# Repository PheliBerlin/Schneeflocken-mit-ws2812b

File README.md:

# Schneeflocken-mit-ws2812b
Deko 2020 mit ws2812b und dem Attiny84

Die Platinen<br>

Nach dem Zusammenbau<br>

Zum Schluß mit Deko<br>

Das ganze ist skalierbar. Vier Sterne mit Deko, schon am Fenster aufgestellt.<br>

Programmiert habe ich das mit der Arduinoumgebung mit der FastLED Bibliothek, da gibt es Anleitungen massenhaft im Netz.

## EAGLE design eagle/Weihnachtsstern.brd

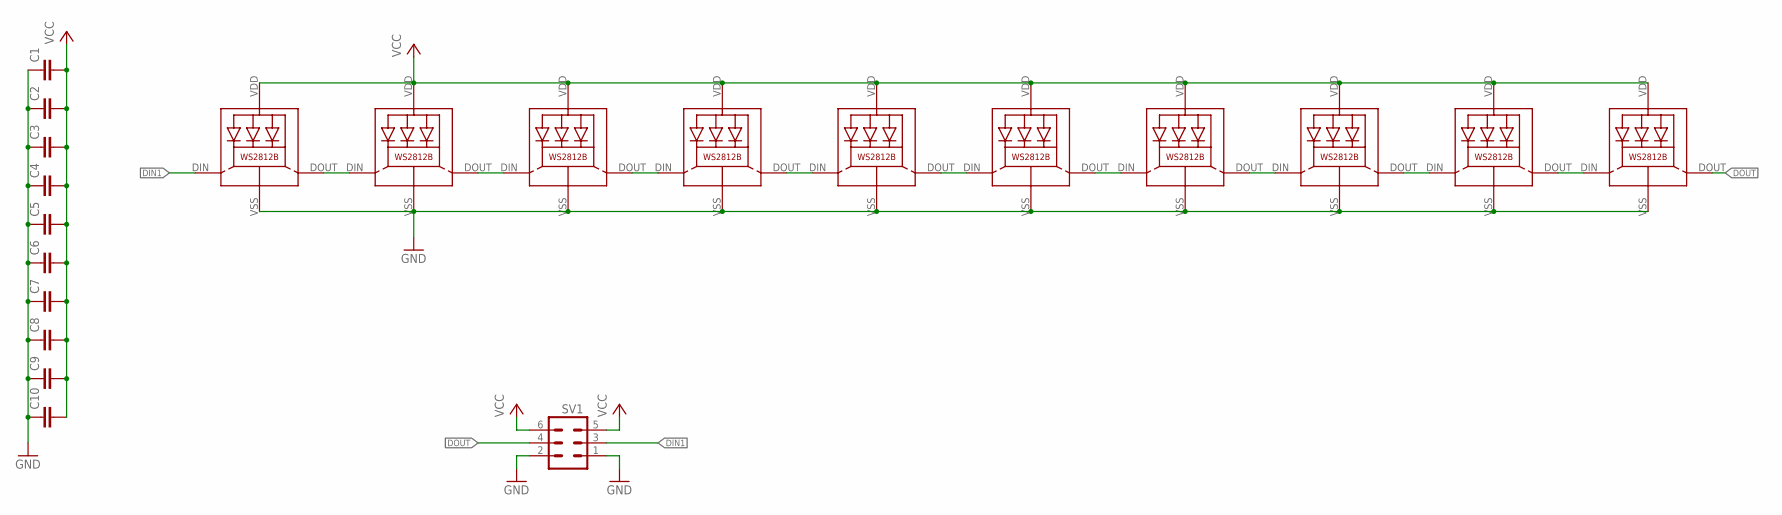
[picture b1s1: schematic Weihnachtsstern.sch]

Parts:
C1, C2, C3, C4, C5, C6, C7, C8, C9, C10: C-EUC0805; C0805
LED1, LED2, LED3, LED4, LED5, LED6, LED7, LED8, LED9, LED10: WS2812B
SV1: MA03-2

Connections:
DIN1: LED1.DIN (DI), SV1.3
DOUT: LED10.DOUT (DO), SV1.4
GND: C1.1, C2.1, C3.1, C4.1, C5.1, C6.1, C7.1, C8.1, C9.1, C10.1, LED1.VSS (GND), LED2.VSS (GND), LED3.VSS (GND), LED4.VSS (GND), LED5.VSS (GND), LED6.VSS (GND), LED7.VSS (GND), LED8.VSS (GND), LED9.VSS (GND), LED10.VSS (GND), SV1.1, SV1.2
unnamed: LED1.DOUT (DO), LED2.DIN (DI)
unnamed: LED2.DOUT (DO), LED3.DIN (DI)
unnamed: LED3.DOUT (DO), LED4.DIN (DI)
unnamed: LED4.DOUT (DO), LED5.DIN (DI)
unnamed: LED5.DOUT (DO), LED6.DIN (DI)
unnamed: LED6.DOUT (DO), LED7.DIN (DI)
unnamed: LED7.DOUT (DO), LED8.DIN (DI)
unnamed: LED8.DOUT (DO), LED9.DIN (DI)
unnamed: LED9.DOUT (DO), LED10.DIN (DI)
VCC: C1.2, C2.2, C3.2, C4.2, C5.2, C6.2, C7.2, C8.2, C9.2, C10.2, LED1.VDD, LED2.VDD, LED3.VDD, LED4.VDD, LED5.VDD, LED6.VDD, LED7.VDD, LED8.VDD, LED9.VDD, LED10.VDD, SV1.5, SV1.6

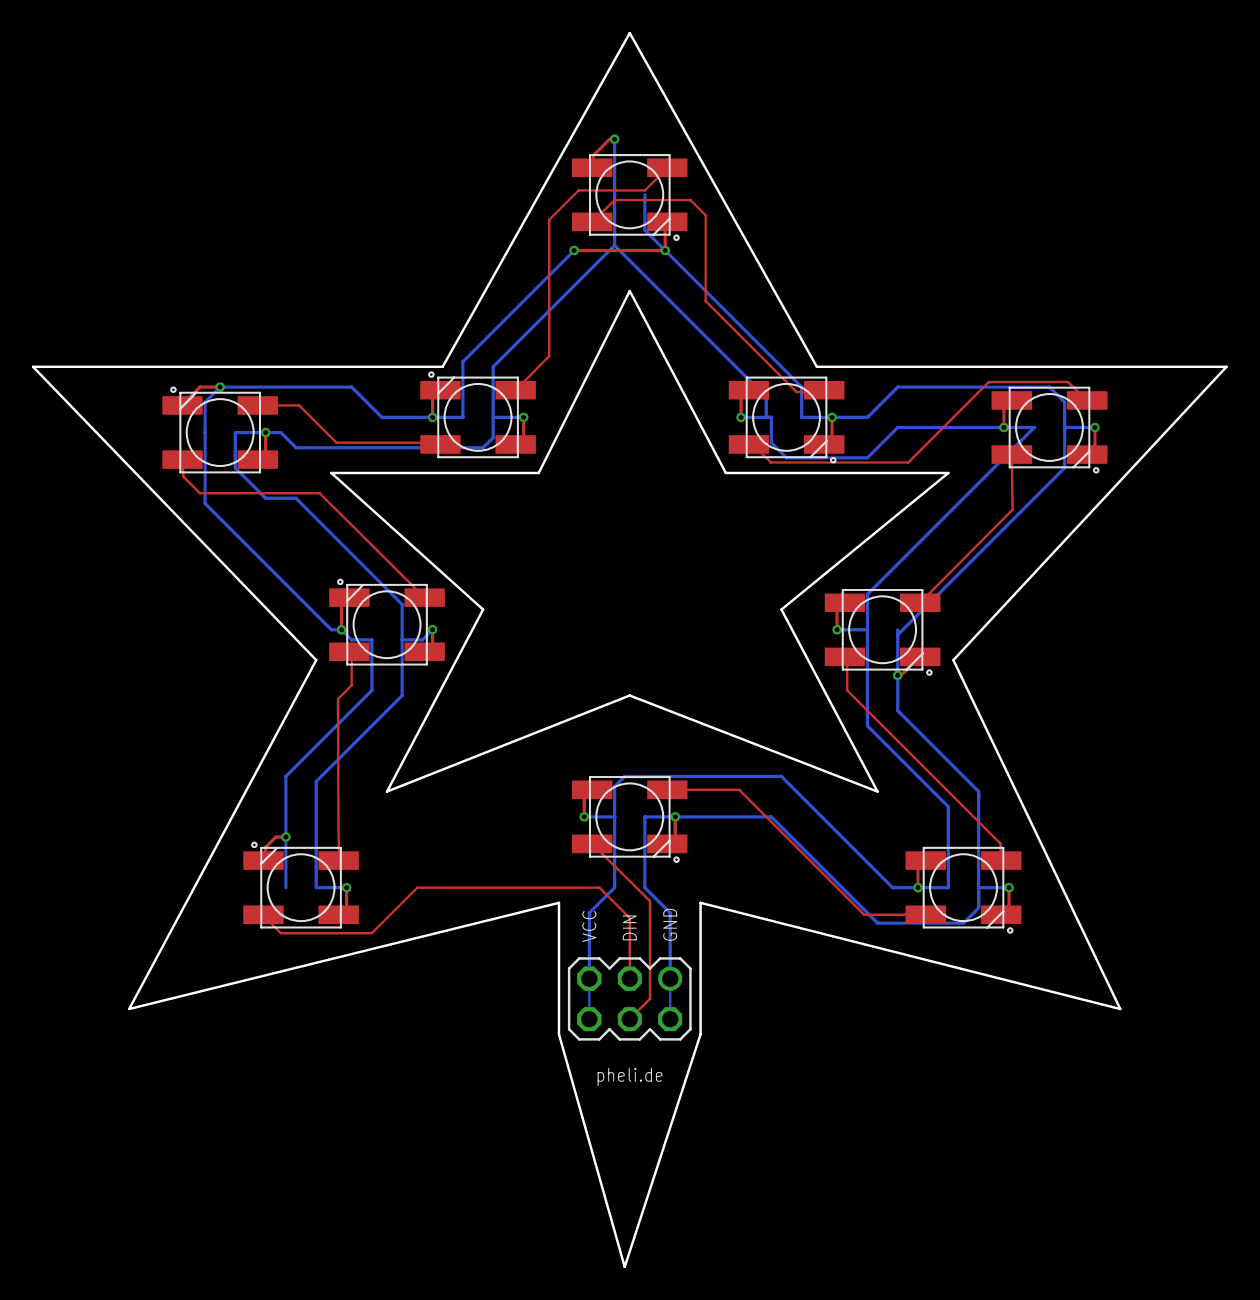
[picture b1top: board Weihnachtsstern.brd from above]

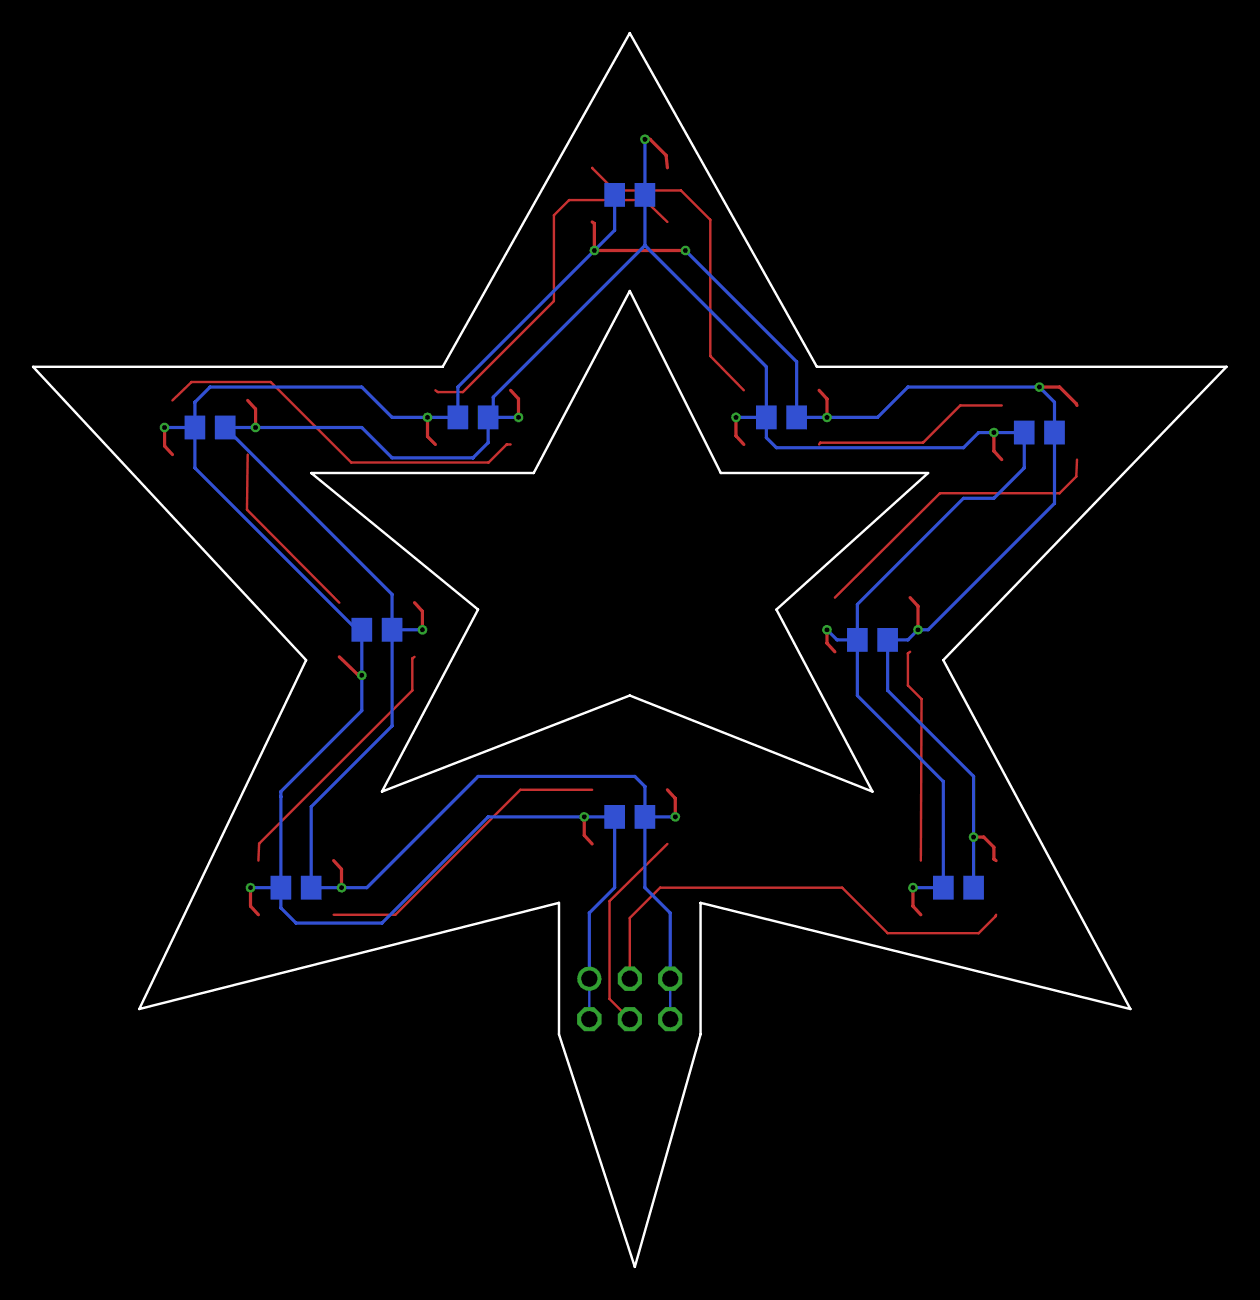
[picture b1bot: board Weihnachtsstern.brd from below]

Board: 2 copper layers, 74.9 x 77.5 mm, 21 parts (10 on the bottom side), 13 nets.

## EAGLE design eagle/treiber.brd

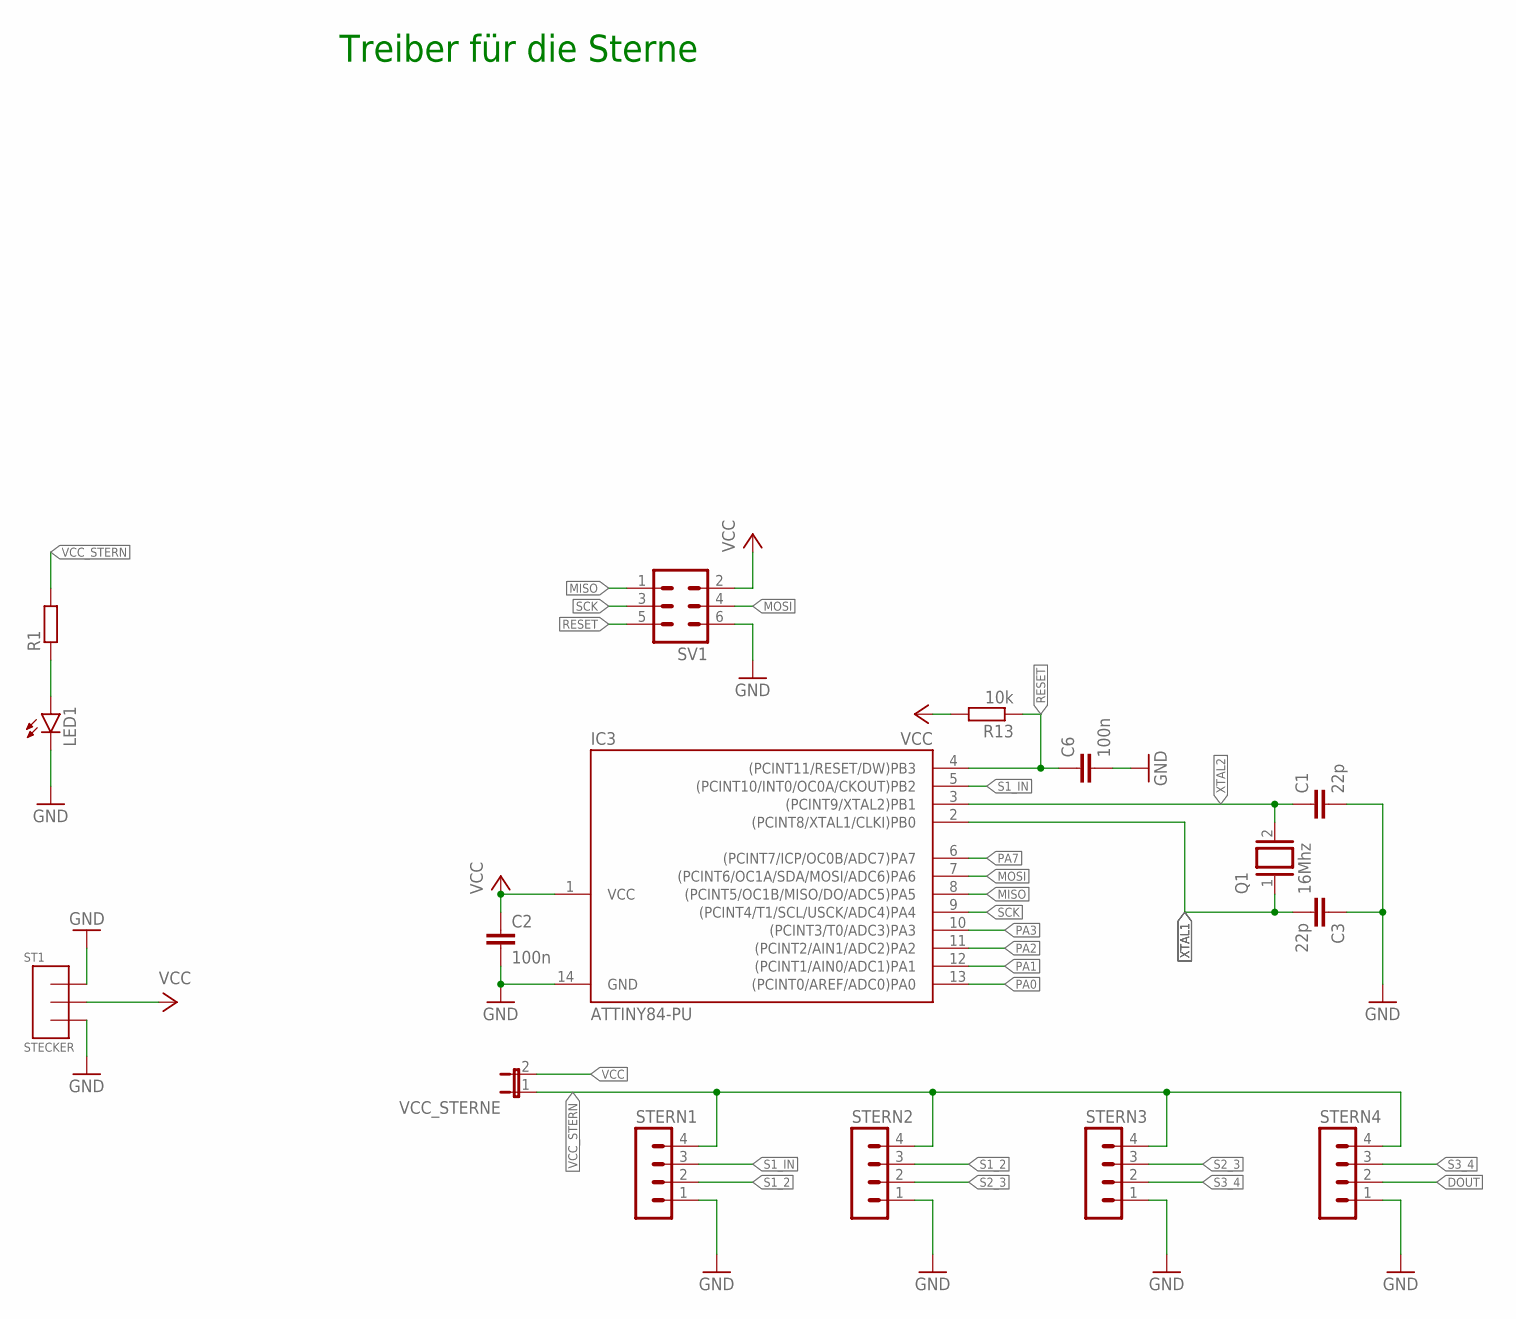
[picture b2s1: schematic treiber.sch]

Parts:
C1, C3: 22p; C025-024X044
C2, C6: 100n; C0805
IC3: ATTINY84-PU; DIL14
LED1: LEDSML0805; SML0805
Q1: 16Mhz; QS
R1: R-EU_R0805; R0805
R13: 10k; R0805
ST1: STECKER; STROMSTECKER
STERN1, STERN2, STERN3, STERN4: MA04-1
SV1: MA03-2
VCC_STERNE: JP1E; JP1

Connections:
DOUT: STERN4.2
GND: C1.2, C2.2, C3.1, C6.2, IC3.14 (GND), LED1.C, ST1.LINKS, ST1.RECHTS, STERN1.1, STERN2.1, STERN3.1, STERN4.1, SV1.6
MISO: IC3.8 ((PCINT5/OC1B/MISO/DO/ADC5)PA5), SV1.1
MOSI: IC3.7 ((PCINT6/OC1A/SDA/MOSI/ADC6)PA6), SV1.4
unnamed: LED1.A, R1.1
PA0: IC3.13 ((PCINT0/AREF/ADC0)PA0)
PA1: IC3.12 ((PCINT1/AIN0/ADC1)PA1)
PA2: IC3.11 ((PCINT2/AIN1/ADC2)PA2)
PA3: IC3.10 ((PCINT3/T0/ADC3)PA3)
PA7: IC3.6 ((PCINT7/ICP/OC0B/ADC7)PA7)
RESET: C6.1, IC3.4 ((PCINT11/RESET/DW)PB3), R13.1, SV1.5
S1_2: STERN1.2, STERN2.3
S1_IN: IC3.5 ((PCINT10/INT0/OC0A/CKOUT)PB2), STERN1.3
S2_3: STERN2.2, STERN3.3
S3_4: STERN3.2, STERN4.3
SCK: IC3.9 ((PCINT4/T1/SCL/USCK/ADC4)PA4), SV1.3
VCC: C2.1, IC3.1 (VCC), R13.2, ST1.INNEN, SV1.2, VCC_STERNE.2
VCC_STERN: R1.2, STERN1.4, STERN2.4, STERN3.4, STERN4.4, VCC_STERNE.1
XTAL1: C3.2, IC3.2 ((PCINT8/XTAL1/CLKI)PB0), Q1.1
XTAL2: C1.1, IC3.3 ((PCINT9/XTAL2)PB1), Q1.2

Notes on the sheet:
Treiber für die Sterne

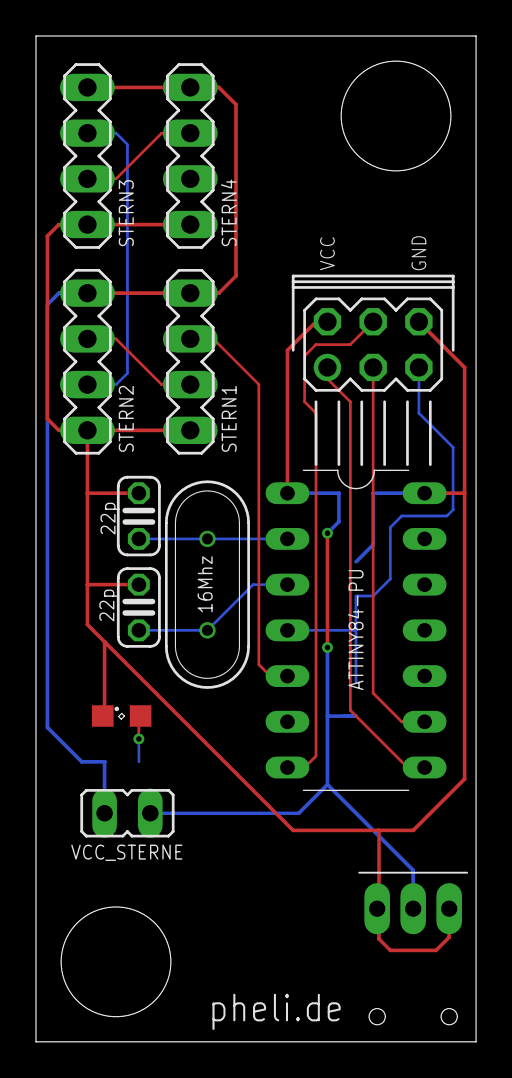
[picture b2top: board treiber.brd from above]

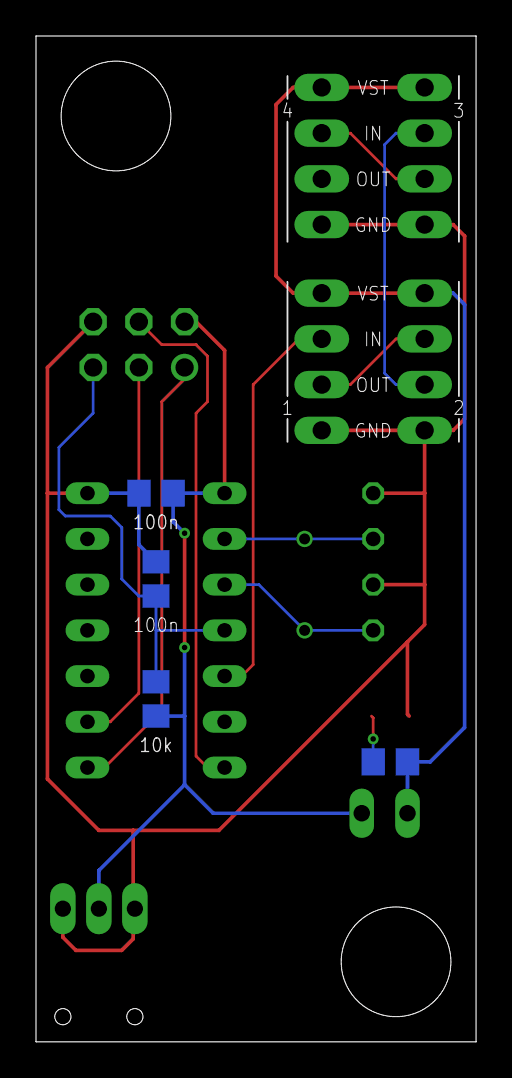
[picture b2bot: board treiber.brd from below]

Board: 2 copper layers, 24.4 x 55.9 mm, 16 parts (4 on the bottom side), 14 nets.

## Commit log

2020-12-09 Create t
